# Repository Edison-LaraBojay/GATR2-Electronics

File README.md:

# GATR2 Electronics

Sensor electronics, manual mecanum drive and encoder localization for a VEX robot.

The active path is tracking wheels -> Pico encoder firmware -> Pi relay ->
Brain localization demo -> spectaGATR. The Brain combines encoder counts with
its VEX IMU heading to compute the pose. The demo also drives eight motors,
two per mecanum wheel, from the controller. Motor ports and reversals must be
configured before driving.

Start with the [localization demo guide](brain/localization-demo/README.md)
for wiring, builds, calibration and visualization. The software builds and
host tests pass; the complete route has not been tested on hardware.

## Active components

| Component | Purpose |
|---|---|
| [Localization demo](brain/localization-demo/README.md) | Manual eight-motor mecanum drive and Brain odometry from two tracking wheels and the VEX IMU. Main setup guide. |
| [Encoder record](encoder-record/README.md) | Shared encoder record format and codec. |
| [Pico firmware](pico/aggreGATR/README.md) | Default `hat2_encoder_demo` sends two encoder channels to the Pi; optional IMU sensor monitors are retained. |
| [Pi encoder relay](pi/encoder-relay/README.md) | Forwards Pico UART records to the Brain USB user port. |
| [spectaGATR](spectaGATR/README.md) | Brain pose publisher, laptop receiver and browser field view. |
| [IMU boards](pcb/IMU/README.md) | Inertial sensor board designs. |
| [Magnetic encoder boards](pcb/MagneticEncoder/README.md) | Tracking-wheel encoder designs. |

## Pico build and upload

From `pico/aggreGATR`, `pio run` builds the encoder sender and
`pio run -t upload` uploads it. The default firmware is `src/main.cpp`; optional
Pico IMU monitors require an explicit `-e hat2_bno08x` or `-e hat2_asm330`.

## Brain host build

```sh
cmake -S brain -B build-brain
cmake --build build-brain --parallel
ctest --test-dir build-brain --output-on-failure
```

The [localization demo guide](brain/localization-demo/README.md) covers its
firmware builds and host tests for the encoder codec, odometry and relay.

## Retired system

The former planning and motor-control libraries, old Brain test applications,
and old Pi runtime and link are retired. Their previous versions remain in
Git history. PCB design history stays tracked with the hardware.

See [documentation](docs/README.md), [PCB overview](pcb/README.md), and
[contribution conventions](CONTRIBUTING.md).

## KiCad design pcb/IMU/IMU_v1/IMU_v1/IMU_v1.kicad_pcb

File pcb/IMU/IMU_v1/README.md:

# IMU v1

[IMU overview](../README.md) · [All PCBs](../../README.md) · [Next project: v2](../IMU_v2/README.md)

**Failed assembly.** The component's bottom-view pin arrangement was used for
the PCB footprint without the required change of view. The resulting footprint
was mirrored, so the device could not be
correctly soldered onto the board. This revision and its Gerber archive retain
that error; the correction is being developed in v2.

Standalone 3.3 V inertial sensor board using the custom ASM330 symbol. It
connects to the carrier over an eight-pin horizontal JST-PH connector carrying
SPI, an interrupt signal, power, and ground.

The intended part is ASM330LHHG1. The schematic's custom symbol does not record the complete ordering
code in its value field.

## Files

- [KiCad project](IMU_v1/IMU_v1.kicad_pro)
- [Schematic](IMU_v1/IMU_v1.kicad_sch)
- [PCB layout](IMU_v1/IMU_v1.kicad_pcb)
- [Saved Gerber archive](IMU_v1/gerbers.zip)
- [Custom symbol](IMU_v1/ASM330.kicad_sym) and [footprint library](IMU_v1/ASM330.pretty/)

The schematic and layout are retained as the record of the failed iteration.
See [v2](../IMU_v2/README.md) for the correction effort.

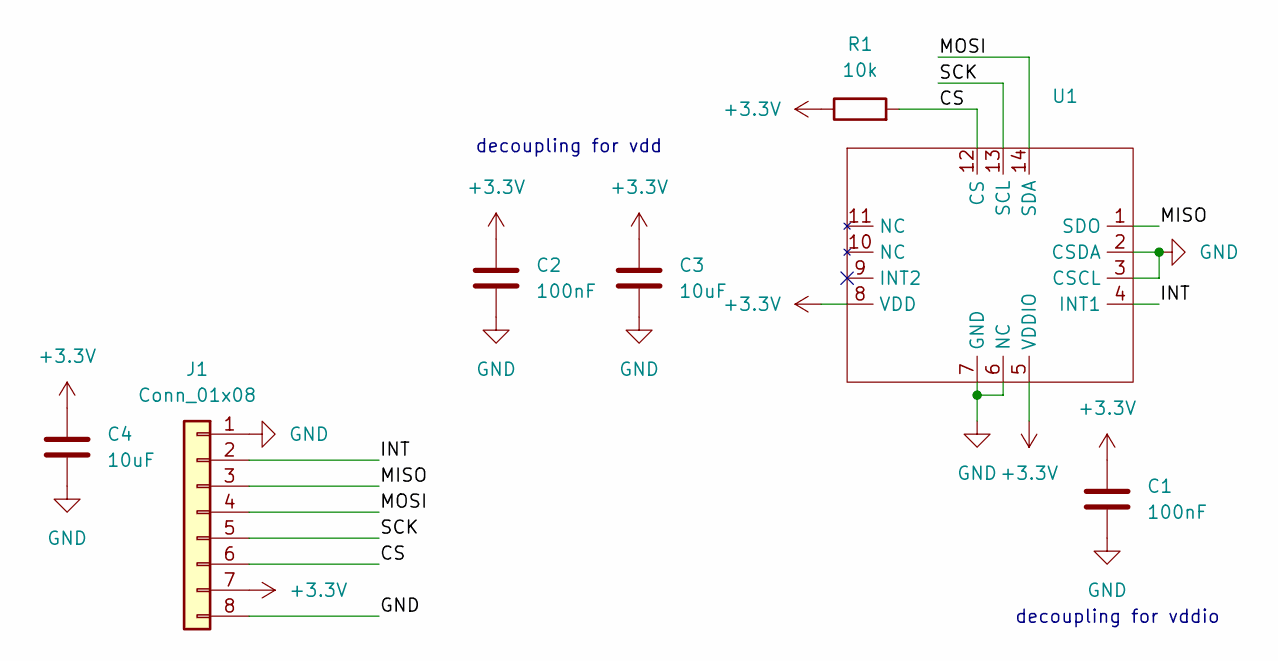
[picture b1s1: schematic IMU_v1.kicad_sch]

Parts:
C1, C2: 100nF; C_0805_2012Metric_Pad1.18x1.45mm_HandSolder
C3, C4: 10uF; C_0805_2012Metric_Pad1.18x1.45mm_HandSolder
J1: Conn_01x08; JST_PH_S8B-PH-K_1x08_P2.00mm_Horizontal
R1: 10k; R_0805_2012Metric_Pad1.20x1.40mm_HandSolder
U1: IMU

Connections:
+3.3V: C1.1, C2.1, C3.1, C4.1, J1.7, R1.1, U1.5 (VDDIO), U1.8 (VDD)
/CS: J1.6, R1.2, U1.12 (CS)
/INT: J1.2, U1.4 (INT1)
/MISO: J1.3, U1.1 (SDO)
/MOSI: J1.4, U1.14 (SDA)
/SCK: J1.5, U1.13 (SCL)
GND: C1.2, C2.2, C3.2, C4.2, J1.1, J1.8, U1.2 (CSDA), U1.3 (CSCL), U1.6 (NC), U1.7 (GND)

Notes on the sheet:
decoupling for vdd
decoupling for vddio

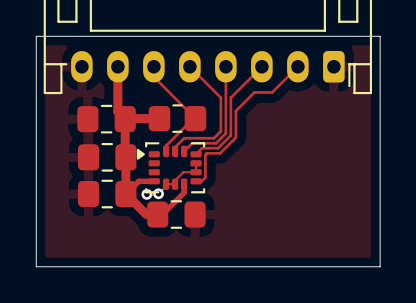
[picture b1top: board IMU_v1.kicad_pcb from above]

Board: 2 copper layers, 19.1 x 12.8 mm, 7 parts (0 on the bottom side), 7 nets.

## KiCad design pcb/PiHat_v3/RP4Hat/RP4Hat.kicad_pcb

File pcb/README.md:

# PCBs

Each active board family has a purpose README and numbered iterations with
schematics, layouts, libraries and design/test notes.

| Board | Purpose |
|---|---|
| [IMU](IMU/README.md) | Inertial measurements for attitude and heading. |
| [Magnetic encoder](MagneticEncoder/README.md) | Compact tracking-wheel encoders. |
| [Pi HAT](PiHat/README.md) | Deprecated Pi/Pico carrier; complete design history retained. |

The complete [Pi HAT family](PiHat/README.md) is deprecated
with the Pi-based system. Its design history remains available for reference.

Choose an iteration and open its `.kicad_pro`. Keep project files and custom
libraries together. The magnetic encoder symbol table contains a historical
workstation-specific library path that may need configuring on another machine.

Follow the [PCB contribution guide](../docs/contributing/README.md) for new
boards and iterations. [Pico acquisition](../pico/README.md) remains active.

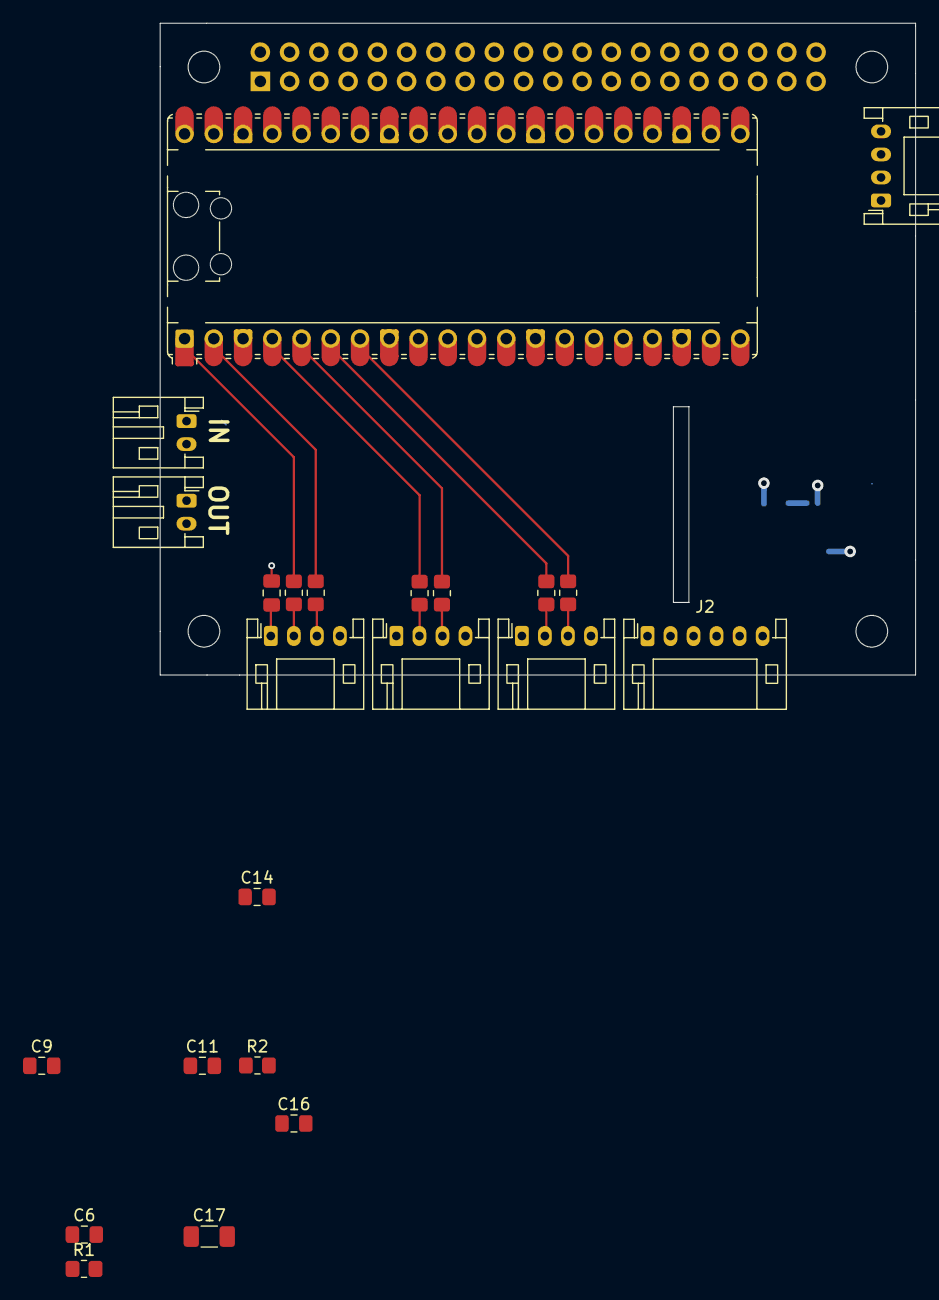
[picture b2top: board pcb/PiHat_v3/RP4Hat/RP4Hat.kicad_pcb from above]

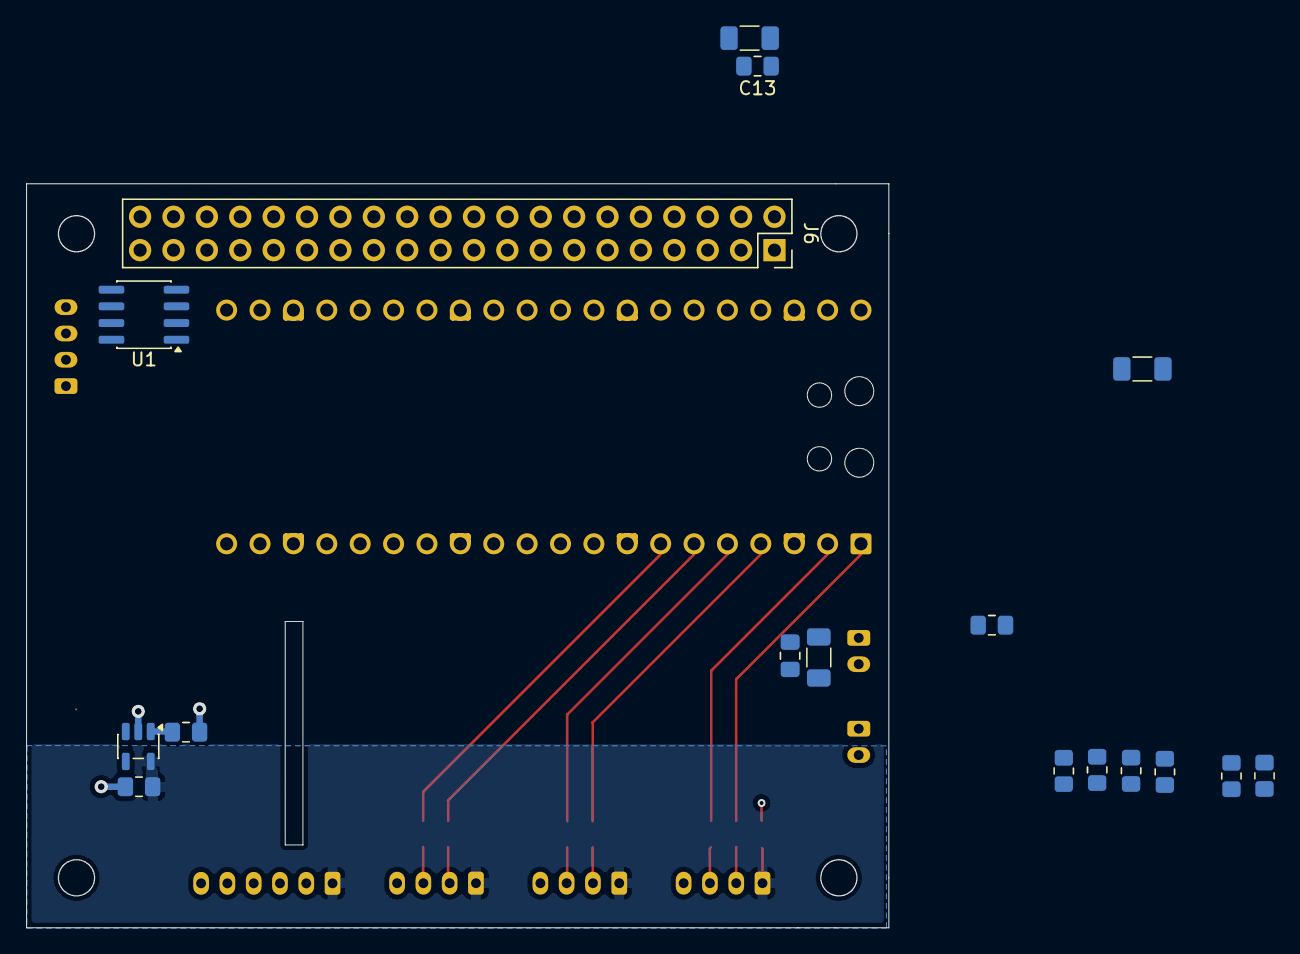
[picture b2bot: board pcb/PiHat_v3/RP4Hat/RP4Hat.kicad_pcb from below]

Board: 4 copper layers, 65.6 x 56.6 mm, 40 parts (17 on the bottom side), 26 nets.

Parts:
A1: RaspberryPi_Pico; RaspberryPi_Pico_Common_Unspecified
C4, C5, C6, C8, C9, C11, C13, C14, C15, C16, C20: 1uF; C_0805_2012Metric_Pad1.18x1.45mm_HandSolder
C7, C10, C12, C17: 22uF; C_1206_3216Metric_Pad1.33x1.80mm_HandSolder
J1, J8, J9, J10: Conn_01x04; JST_PH_S4B-PH-K_1x04_P2.00mm_Horizontal
J2: Conn_01x06; JST_PH_S6B-PH-K_1x06_P2.00mm_Horizontal
J5, J11: Conn_01x02; JST_PH_S2B-PH-K_1x02_P2.00mm_Horizontal
J6: Raspberry_Pi_4; PinSocket_2x20_P2.54mm_Vertical
R1, R2, R8, R9, R10, R11, R12, R13: 10k; R_0805_2012Metric_Pad1.20x1.40mm_HandSolder
R15, R16, R17, R18, R19, R20: 100; R_0805_2012Metric_Pad1.20x1.40mm_HandSolder
U1: ST3485ECDR; SOIC-8_3.9x4.9mm_P1.27mm
U2: AP2112K-3.3; SOT-23-5

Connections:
+3.3V: C4.1, C6.1, C9.1, C11.1, C14.1, C15.1, J2.1, J8.1, J9.1, J10.1, R2.1, U1.8 (VCC), U2.5 (VOUT)
+5V: A1.39 (VSYS), C5.1, C7.1, C8.1, C10.1, C12.1, C13.1, C16.1, C17.1, C20.1, J5.1, J6.2 (5V), J6.4 (5V), J11.1, U2.1 (VIN), U2.3 (EN)
/A: J1.1, U1.6 (A)
/B: J1.2, U1.7 (B)
/EN: J6.31 (GPCLK2/GPIO06), R1.1, U1.2 (~RE), U1.3 (DE)
/IMU0_CS: A1.12 (GPIO9), J2.5, R2.2
/IMU0_MISO: A1.11 (GPIO8), J2.2
/IMU0_MOSI: A1.15 (GPIO11), J2.3
/IMU0_SCK: A1.14 (GPIO10), J2.4
/PICORX: A1.22 (GPIO17), J6.8 (GPIO14/UART_TXD)
/PICOTX: A1.21 (GPIO16), J6.10 (GPIO15/UART_RXD)
/RSRX: J6.33 (GPIO13/PWM1), U1.1 (R)
/RSTX: J6.32 (GPIO12/PWM0), U1.4 (D)
/TW0_A: A1.1 (GPIO0), R8.1, R15.2
/TW0_B: A1.2 (GPIO1), R9.1, R16.2
/TW1_A: A1.4 (GPIO2), R10.1, R17.2
/TW1_B: A1.5 (GPIO3), R11.1, R18.2
/TW2_A: A1.6 (GPIO4), R12.1, R19.2
/TW2_B: A1.7 (GPIO5), R13.1, R20.2
GND: A1.3 (GND), A1.8 (GND), A1.13 (GND), A1.18 (GND), A1.23 (GND), A1.28 (GND), A1.38 (GND), C4.2, C5.2, C6.2, C7.2, C8.2, C9.2, C10.2, C11.2, C12.2, C13.2, C14.2, C15.2, C16.2, C17.2, C20.2, J1.3, J2.6, J5.2, J6.6 (GND), J6.9 (GND), J6.14 (GND), J6.20 (GND), J6.25 (GND), J6.30 (GND), J6.34 (GND), J6.39 (GND), J8.4, J9.4, J10.4, J11.2, R1.2, R8.2, R9.2, R10.2, R11.2, R12.2, R13.2, U1.5 (GND), U2.2 (GND)
unnamed: J8.2, R15.1
unnamed: J8.3, R16.1
unnamed: J9.2, R17.1
unnamed: J9.3, R18.1
unnamed: J10.2, R19.1
unnamed: J10.3, R20.1

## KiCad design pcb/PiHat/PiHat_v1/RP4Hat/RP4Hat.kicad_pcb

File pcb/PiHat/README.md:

# Pi HAT

[All PCBs](../README.md)

**Deprecated board family.** These Pi carrier designs are retained with their
complete iteration history, schematics, layouts and libraries for reference.
They are no longer the target architecture for new hardware.

A carrier board that plugs directly into the Raspberry Pi's 40-pin header to
minimize loose wiring and provide a stable connection. Dedicated ports connect
the robot's sensors and peripherals without a collection of individual jumper
wires between the Pi and the acquisition hardware.

The HAT brings together the Pi, Pico acquisition module, tracking-wheel
connections, and the V5 Brain communication interface. Later revisions add an
IMU connection, sensor power regulation, fan power, and provisions for other
peripherals. Port choices can evolve with the needs of future robots and
seasons.

Mechanical clearance, power distribution, and readable schematics are part of
the design alongside the electrical interfaces. Each iteration documents its
specific connections, layout changes, and bench results.

## Iterations

| Revision | Changes and status |
|---|---|
| [Pi HAT v1](PiHat_v1/README.md) | Initial two-layer design. Tracking-wheel acquisition and Brain communication tested successfully. |
| [Pi HAT v2](PiHat_v2/README.md) | Four layers, a dedicated 3.3 V LDO, and an SPI IMU port. Initial power-up and LDO operation confirmed; full testing pending. |
| [Pi HAT v3](PiHat_V3/README.md) | In progress: revised routing, separate power input/fan output, a camera-ribbon slot, and schematic sheets. Audio and LED interfaces are planned. |

Revision names follow the folders. The older board silkscreens use different
labels: `PiHat_v1` says `V0`, and `PiHat_v2` says `V1`.

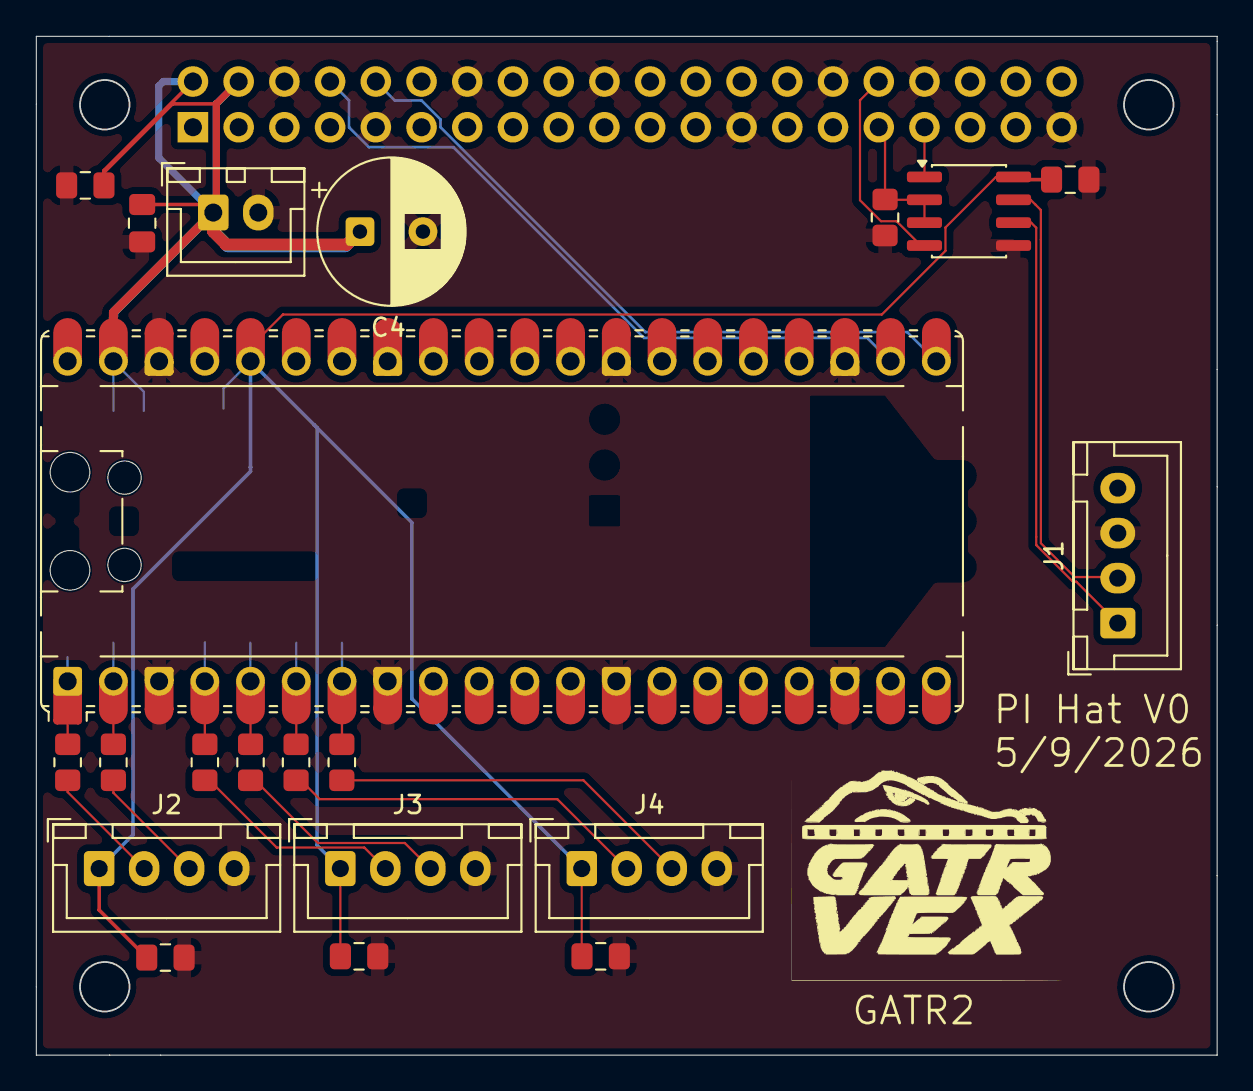
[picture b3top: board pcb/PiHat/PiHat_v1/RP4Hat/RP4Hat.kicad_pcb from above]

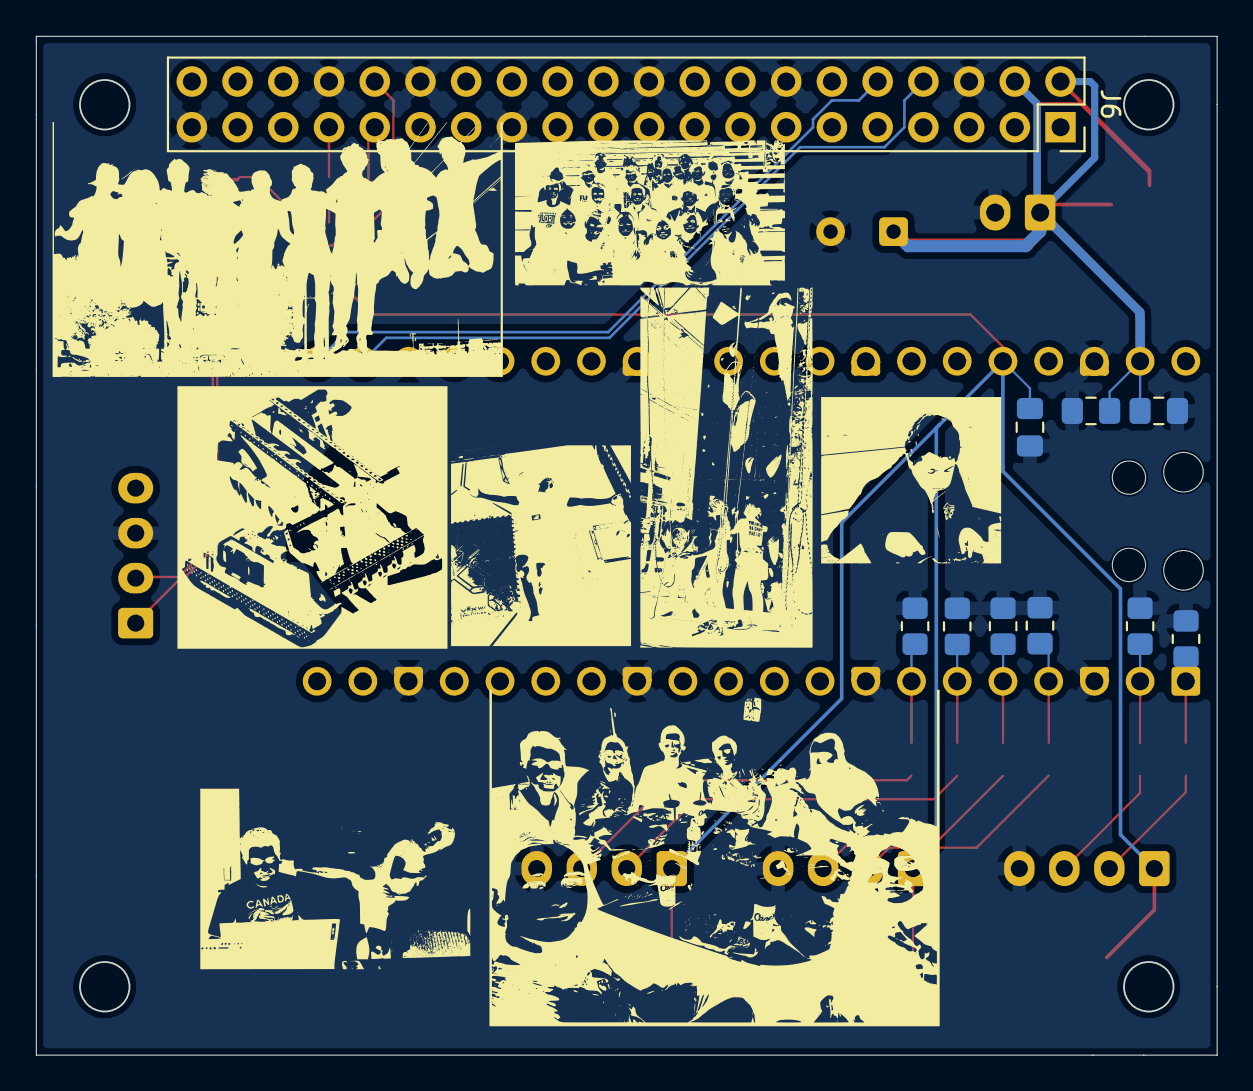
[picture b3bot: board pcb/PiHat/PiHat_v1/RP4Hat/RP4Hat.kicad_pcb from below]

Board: 2 copper layers, 65.6 x 56.6 mm, 31 parts (10 on the bottom side), 22 nets.

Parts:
A1: RaspberryPi_Pico; RaspberryPi_Pico_Common_Unspecified
C1, C2, C3, C5, C6, C8, C9: 1uF; C_0805_2012Metric_Pad1.18x1.45mm_HandSolder
C4: 400uF; CP_Radial_D8.0mm_P3.50mm
C7, C10: 22uF; C_0805_2012Metric_Pad1.18x1.45mm_HandSolder
J1, J2, J3, J4: Conn_01x04; JST_XH_B4B-XH-A_1x04_P2.50mm_Vertical
J5: Conn_01x02; JST_XH_B2B-XH-A_1x02_P2.50mm_Vertical
J6: Raspberry_Pi_4; PinSocket_2x20_P2.54mm_Vertical
R1, R8, R9, R10, R11, R12, R13: 10k; R_0805_2012Metric_Pad1.20x1.40mm_HandSolder
R2, R3, R4, R5, R6, R7: 100; R_0805_2012Metric_Pad1.20x1.40mm_HandSolder
U1: SN65HVD11HD; SOIC-8_3.9x4.9mm_P1.27mm

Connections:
+3.3V: A1.36 (3V3), C1.1, C2.1, C3.1, C6.1, C9.1, J2.1, J3.1, J4.1, U1.8 (VCC)
+5V: A1.39 (VSYS), C4.1, C5.1, C7.1, C8.1, C10.1, J5.1, J6.2 (5V), J6.4 (5V)
/A: J1.1, U1.6 (A)
/A0: A1.1 (GPIO0), R2.2, R8.1
/A1: A1.4 (GPIO2), R4.2, R10.1
/A2: A1.6 (GPIO4), R6.2, R12.1
/B: J1.2, U1.7 (B)
/B0: A1.2 (GPIO1), R3.2, R9.1
/B1: A1.5 (GPIO3), R5.2, R13.1
/B2: A1.7 (GPIO5), R7.2, R11.1
/EN: J6.31 (GPCLK2/GPIO06), R1.1, U1.2 (~RE), U1.3 (DE)
/PICORX: A1.22 (GPIO17), J6.8 (GPIO14/UART_TXD)
/PICOTX: A1.21 (GPIO16), J6.10 (GPIO15/UART_RXD)
/RSRX: J6.33 (GPIO13/PWM1), U1.1 (R)
/RSTX: J6.32 (GPIO12/PWM0), U1.4 (D)
GND: A1.3 (GND), A1.8 (GND), A1.13 (GND), A1.18 (GND), A1.23 (GND), A1.28 (GND), A1.38 (GND), C1.2, C2.2, C3.2, C4.2, C5.2, C6.2, C7.2, C8.2, C9.2, C10.2, J1.3, J2.4, J3.4, J4.4, J5.2, J6.6 (GND), J6.9 (GND), J6.14 (GND), J6.20 (GND), J6.25 (GND), J6.30 (GND), J6.34 (GND), J6.39 (GND), R1.2, R8.2, R9.2, R10.2, R11.2, R12.2, R13.2, U1.5 (GND)
unnamed: J2.2, R2.1
unnamed: J2.3, R3.1
unnamed: J3.2, R4.1
unnamed: J3.3, R5.1
unnamed: J4.2, R6.1
unnamed: J4.3, R7.1

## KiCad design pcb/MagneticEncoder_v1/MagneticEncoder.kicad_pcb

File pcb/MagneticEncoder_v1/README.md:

# Magnetic encoder v1

[All PCBs](../README.md)

AS5047P-ATSM magnetic rotary encoder board for tracking-wheel displacement.
Its four-pin horizontal JST-PH harness carries 3.3 V, A, B, and ground to the
acquisition board. Separate solder connections expose the SPI signals.

The wheel interface uses A/B quadrature; the encoder's index/PWM pin is
unconnected in this design. This is the only magnetic encoder revision in the
repository.

## Files

- [KiCad project](MagneticEncoder.kicad_pro)
- [Schematic](MagneticEncoder.kicad_sch)
- [PCB layout](MagneticEncoder.kicad_pcb)
- [Footprint library](MagnetEncoderFootprint.pretty/)
- [Symbol library table](sym-lib-table)

The AS5047P symbol library entry uses a workstation-specific path, although the
schematic contains an embedded copy of the symbol. See the
[PCB overview](../README.md) for library-path and fabrication-status notes.

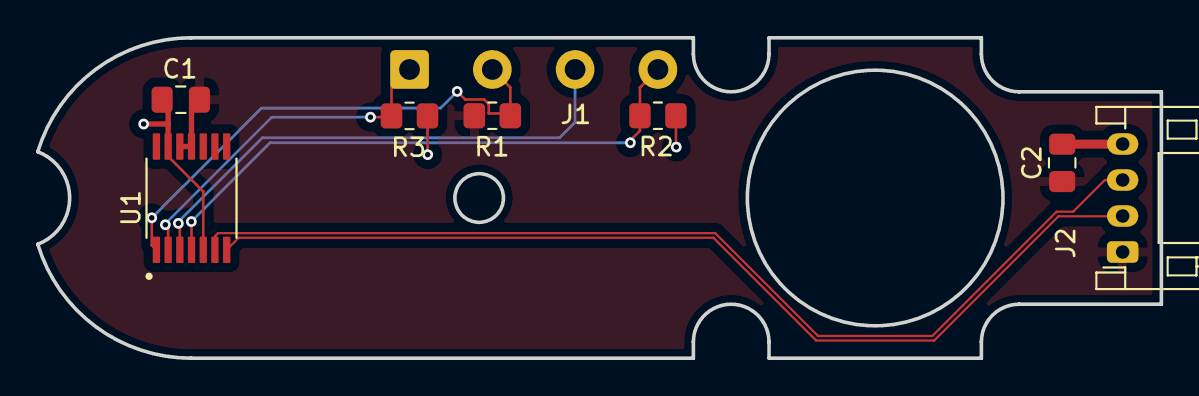
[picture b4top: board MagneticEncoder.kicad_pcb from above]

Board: 2 copper layers, 62.4 x 17.8 mm, 8 parts (0 on the bottom side), 8 nets.

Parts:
C1: 1uF; C_0805_2012Metric_Pad1.18x1.45mm_HandSolder
C2: 0.1uF; C_0805_2012Metric_Pad1.18x1.45mm_HandSolder
J1: Conn_01x04; SolderWire-0.5sqmm_1x04_P4.6mm_D0.9mm_OD2.1mm
J2: Conn_01x04; JST_PH_S4B-PH-K_1x04_P2.00mm_Horizontal
R1, R2, R3: 10k; R_0805_2012Metric_Pad1.20x1.40mm_HandSolder
U1: AS5047P-ATSM; MagneticEncoder

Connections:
+3.3V: C1.1, C2.1, J2.1, R1.1, U1.11 (VDD), U1.12 (VDD3V3)
/A: J2.2, U1.7 (A)
/B: J2.3, U1.6 (B)
/CLK: J1.1, R3.1, U1.2 (CLK)
/CS: J1.2, R1.2, U1.1 (CSN)
/MISO: J1.3, U1.3 (MISO)
/MOSI: J1.4, R2.1, U1.4 (MOSI)
GND: C1.2, C2.2, J2.4, R2.2, R3.2, U1.5 (TEST), U1.13 (GND)
